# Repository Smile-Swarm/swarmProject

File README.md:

# swarmProject
Design for cloud-based rovers to perform image processing over a wireless distributed-computing framework using Jetson Nano, Zigbees and Arduino.

**Please refer to the [wiki](https://github.com/Smile-Swarm/swarmProject/wiki) for more information

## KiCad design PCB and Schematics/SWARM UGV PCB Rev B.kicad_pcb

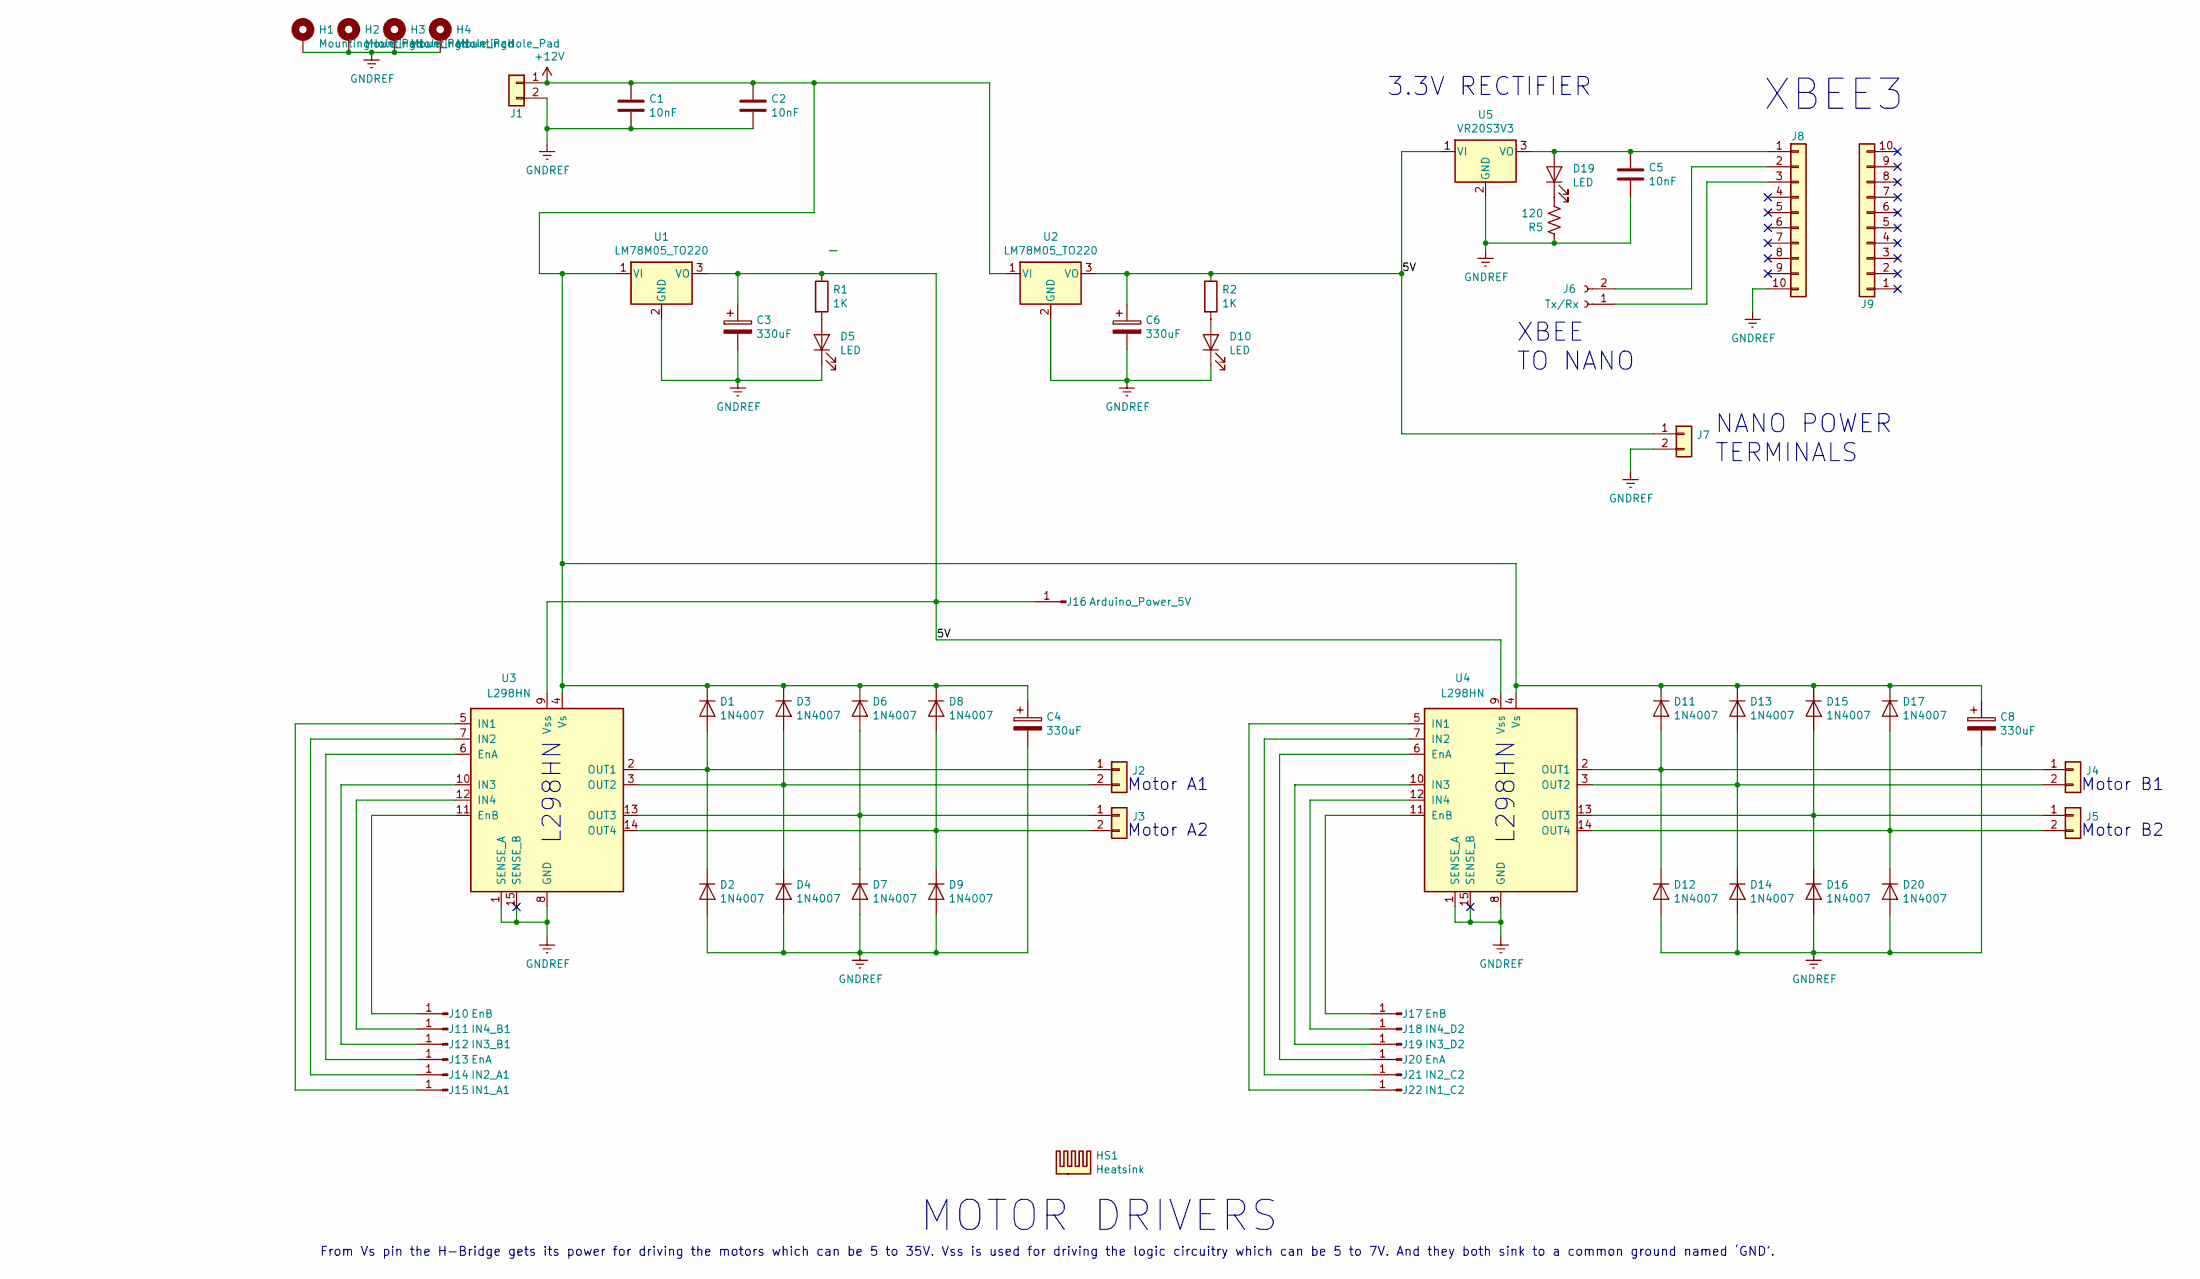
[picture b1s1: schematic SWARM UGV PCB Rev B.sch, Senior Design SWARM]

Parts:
C1, C2, C5: 10nF; C_Disc_D5.0mm_W2.5mm_P5.00mm
C3, C4, C6, C8: 330uF; CP_Radial_D5.0mm_P2.00mm
D1, D2, D3, D4, D6, D7, D8, D9, D11, D12, D13, D14, D15, D16, D17, D20: 1N4007; D_DO-41_SOD81_P10.16mm_Horizontal
D5, D10, D19: LED; LED_D3.0mm
H1, H2, H3, H4: MountingHole_Pad; MountingHole_3.2mm_M3_Pad
HS1: Heatsink
J1, J7: SolderWirePad_1x02_P5.08mm_Drill1.5mm
J2, J3, J4, J5: PinSocket_1x02_P2.54mm_Vertical
J6: Tx/Rx; PinHeader_1x02_P2.54mm_Vertical
J8, J9: PinSocket_1x10_P2.00mm_Vertical
J10, J17: EnB; PinHeader_1x01_P2.54mm_Vertical
J11: IN4_B1; PinHeader_1x01_P2.54mm_Vertical
J12: IN3_B1; PinHeader_1x01_P2.54mm_Vertical
J13, J20: EnA; PinHeader_1x01_P2.54mm_Vertical
J14: IN2_A1; PinHeader_1x01_P2.54mm_Vertical
J15: IN1_A1; PinHeader_1x01_P2.54mm_Vertical
J16: Arduino_Power_5V; PinHeader_1x01_P2.54mm_Vertical
J18: IN4_D2; PinHeader_1x01_P2.54mm_Vertical
J19: IN3_D2; PinHeader_1x01_P2.54mm_Vertical
J21: IN2_C2; PinHeader_1x01_P2.54mm_Vertical
J22: IN1_C2; PinHeader_1x01_P2.54mm_Vertical
R1, R2: 1K; R_Axial_DIN0207_L6.3mm_D2.5mm_P10.16mm_Horizontal
R5: 120; R_Axial_DIN0207_L6.3mm_D2.5mm_P10.16mm_Horizontal
U1, U2: LM78M05_TO220; TO-220-3_Vertical
U3, U4: L298HN; TO-220-15_P2.54x2.54mm_StaggerOdd_Lead4.58mm_Vertical
U5: VR20S3V3; TO-220-3_Vertical

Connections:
+12V: C1.1, C2.1, C4.1, C8.1, D1.1 (K), D3.1 (K), D6.1 (K), D8.1 (K), D11.1 (K), D13.1 (K), D15.1 (K), D17.1 (K), J1.1, U1.1 (VI), U2.1 (VI), U3.4 (Vs), U4.4 (Vs)
/5V: C3.1, C6.1, J7.1, J16.1, R1.1, R2.1, U1.3 (VO), U2.3 (VO), U3.9 (Vss), U4.9 (Vss), U5.1 (VI)
GNDREF: C1.2, C2.2, C3.2, C4.2, C5.2, C6.2, C8.2, D2.2 (A), D4.2 (A), D5.1 (K), D7.2 (A), D9.2 (A), D10.1 (K), D12.2 (A), D14.2 (A), D16.2 (A), D20.2 (A), H1.1, H2.1, H3.1, H4.1, J1.2, J7.2, J8.10, R5.2, U1.2 (GND), U2.2 (GND), U3.1 (SENSE_A), U3.8 (GND), U3.15 (SENSE_B), U4.1 (SENSE_A), U4.8 (GND), U4.15 (SENSE_B), U5.2 (GND)
unnamed: C5.1, D19.2 (A), J8.1, U5.3 (VO)
unnamed: D1.2 (A), D2.1 (K), J2.1, U3.2 (OUT1)
unnamed: D3.2 (A), D4.1 (K), J2.2, U3.3 (OUT2)
unnamed: D5.2 (A), R1.2
unnamed: D6.2 (A), D7.1 (K), J3.1, U3.13 (OUT3)
unnamed: D8.2 (A), D9.1 (K), J3.2, U3.14 (OUT4)
unnamed: D10.2 (A), R2.2
unnamed: D11.2 (A), D12.1 (K), J4.1, U4.2 (OUT1)
unnamed: D13.2 (A), D14.1 (K), J4.2, U4.3 (OUT2)
unnamed: D15.2 (A), D16.1 (K), J5.1, U4.13 (OUT3)
unnamed: D17.2 (A), D20.1 (K), J5.2, U4.14 (OUT4)
unnamed: D19.1 (K), R5.1
unnamed: J6.1, J8.3
unnamed: J6.2, J8.2
unnamed: J10.1, U3.11 (EnB)
unnamed: J11.1, U3.12 (IN4)
unnamed: J12.1, U3.10 (IN3)
unnamed: J13.1, U3.6 (EnA)
unnamed: J14.1, U3.7 (IN2)
unnamed: J15.1, U3.5 (IN1)
unnamed: J17.1, U4.11 (EnB)
unnamed: J18.1, U4.12 (IN4)
unnamed: J19.1, U4.10 (IN3)
unnamed: J20.1, U4.6 (EnA)
unnamed: J21.1, U4.7 (IN2)
unnamed: J22.1, U4.5 (IN1)

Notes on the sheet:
XBEE3
XBEE TO NANO
3.3V RECTIFIER
MOTOR DRIVERS
NANO POWER TERMINALS
From Vs pin the H-Bridge gets its power for driving the motors which can be 5 to 35V. Vss is used for driving the logic circuitry which can be 5 to 7V. And they both sink to a common ground named ‘GND’.
Motor A2
Motor A1
L298HN
Motor B1
Motor B2

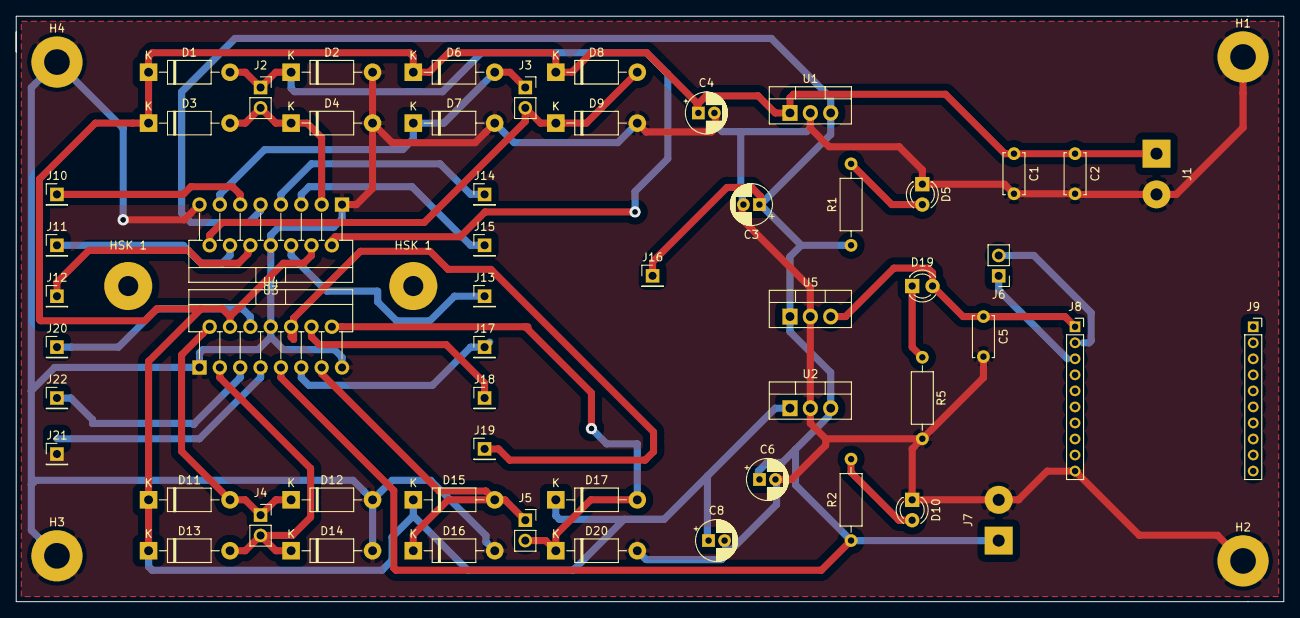
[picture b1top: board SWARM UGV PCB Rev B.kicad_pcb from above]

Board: 2 copper layers, 158.1 x 73.0 mm, 62 parts (0 on the bottom side), 29 nets.

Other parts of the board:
HSK 1, HSK 1#2: HSK1; SolderWirePad_1x01_Drill2.5mm

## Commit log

2020-06-16 Update README.md
    Adding description and problem statement
2020-06-24 Create Husky
2020-06-24 Create simplemove
2020-06-24 Rename simplemove to simplemove.py
2020-06-24 Rename README to README.md
2020-07-03 Creating a new folder
    For documentation
2020-07-03 Uploading files
    Writing pdd and pmp
2020-07-04 Added files into documentation
    Addition(s): Block diagram
    -Block Diagram
    -System Block Diagram
    -MPI Structure
2020-07-04 Update the README.md
    nothin much here
2020-07-17 Created mpi folder and readme
    For the project
2020-07-20 Created a hello world for MPI
2020-07-21 Created mpiRingPtP.c
2020-07-21 Renaming mpiRingPtP.c
2020-07-22 Rename Communication/Listener.py to Communication/SimpleComms/Listener.py
2020-07-22 Rename Communication/README.md to Communication/SimpleComms/README.md
2020-07-22 Rename Communication/Talker.py to Communication/SimpleComms/Talker.py
2020-07-24 Created masterbot.py
    main talker
2020-07-24 Created workerbot.py
    Version 1
2020-07-24 Create laser.launch
    This is the launch file for the laser_values package
2020-07-24 Create scan.py
    Python scrip that extracts laser data from rviz and constantly displays the value of the laser depth at 0 degrees, 90 degrees, and 180 degrees to the robot.
2020-08-04 Created masterbot_V2.py
    Version 2 of master robot
2020-08-04 Create worker_aV2.py
    Made the version 2 of worker a_robot
2020-08-04 Create worker_bV2.py
    Made version 2 of worker b_robot
2020-08-04 Update README.md
    Goals for the week of Aug. 7th
2020-08-06 Created masterbot_V3.py
    Addition of enabling sending a full matrix as well as a vector
2020-08-06 Create worker_aV3.py
    Listening to a vector as well as a full matrix
2020-08-06 Updated masterbolo_V3.py
    sending second row of A matrix to b inorder to do some calculations
2020-08-06 Created worker_bV3.py
    Listens to master bot for a vector and a matrix
2020-08-12 Create test
2020-08-12 Update and rename test to README
2020-08-12 Updated masterbot_V3.py
2020-08-12 Updated worker_aV3.py
2020-08-20 Create matrix_mult.launch
    Launch file to call the other launches we want for the simulation
2020-08-20 Created leader.launch
    calls the specific python script for the master bot
2020-08-20 created follower.launch
    for worker a, running the worker a talker and listener
2020-08-20 Created follower2.launch
2020-08-25 Train your own object detection model
2020-08-27 Update objectLocalization.py
    This script was only used to replicate the localization of a husky robot from an aerial POV using a Logitech C920 camera.
    The intrinsic/extrinsic properties were taken from the previous group (who used MATLAB instead) and the results matched the same results they calculated.
2020-09-01 Create teb_course.launch
    Set kinect_enabled to "true" to enable Kinect camera on the husky
2020-09-01 Rename cameras and sensors/husky/husky_launch/teb_course.launch to Cameras and Sensors/husky/husky_launch/teb_course.launch
2020-09-01 Create teb_course.launch
    Set kinect_enables to "true" to activate Kinect camera on husky
2020-09-03 Create messageTest.py
    For throttling
2020-09-03 Created throttleListener.py
    For throttling simulation
2020-09-03 Rename empty_world.launch to husky_empty_world.launch
2020-09-15 Create receive_sim_cam.py
    Big thanks to (Ramiz Hanan)[https://github.com/RamizHanan] for creating the original script and helping me modify it for this project.
2021-01-12 Create Arduino
2021-01-12 Create Jetson Nano
2021-01-12 Create final
2021-01-12 Create PCB and Schematics
2021-02-08 Create READEME
